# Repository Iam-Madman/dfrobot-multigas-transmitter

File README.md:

# DFRobot Multi-Gas Transmitter

An industrial-grade, multi-phase gas monitoring system implementing the Modbus RTU protocol over RS-485. This repository serves as a monorepo containing everything from the initial rapid hardware prototypes to production-ready firmware and hardware fabrication files.

---

## Repository Structure

The project separates hardware development from firmware development ecosystems across distinct execution phases:

```text
.
├── fabrication/                 
└── firmware/
    ├── arduino_nano_firmware/   
    └── bluepill_firmware/

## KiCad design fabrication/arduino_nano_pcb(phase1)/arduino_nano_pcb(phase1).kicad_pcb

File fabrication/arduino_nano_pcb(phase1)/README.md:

## Phase 1 Hardware Prototyping

The Phase 1 board utilizes an Arduino Nano baseboard designed for rapid validation of the TM1637 display interface and the DFRobot gas sensor lines. The traces have been widened to optimized thresholds (0.8mm–1.0mm) to allow for reliable manual mechanical isolation milling.

### Board Previews

| |
|---|
|  |
|  |

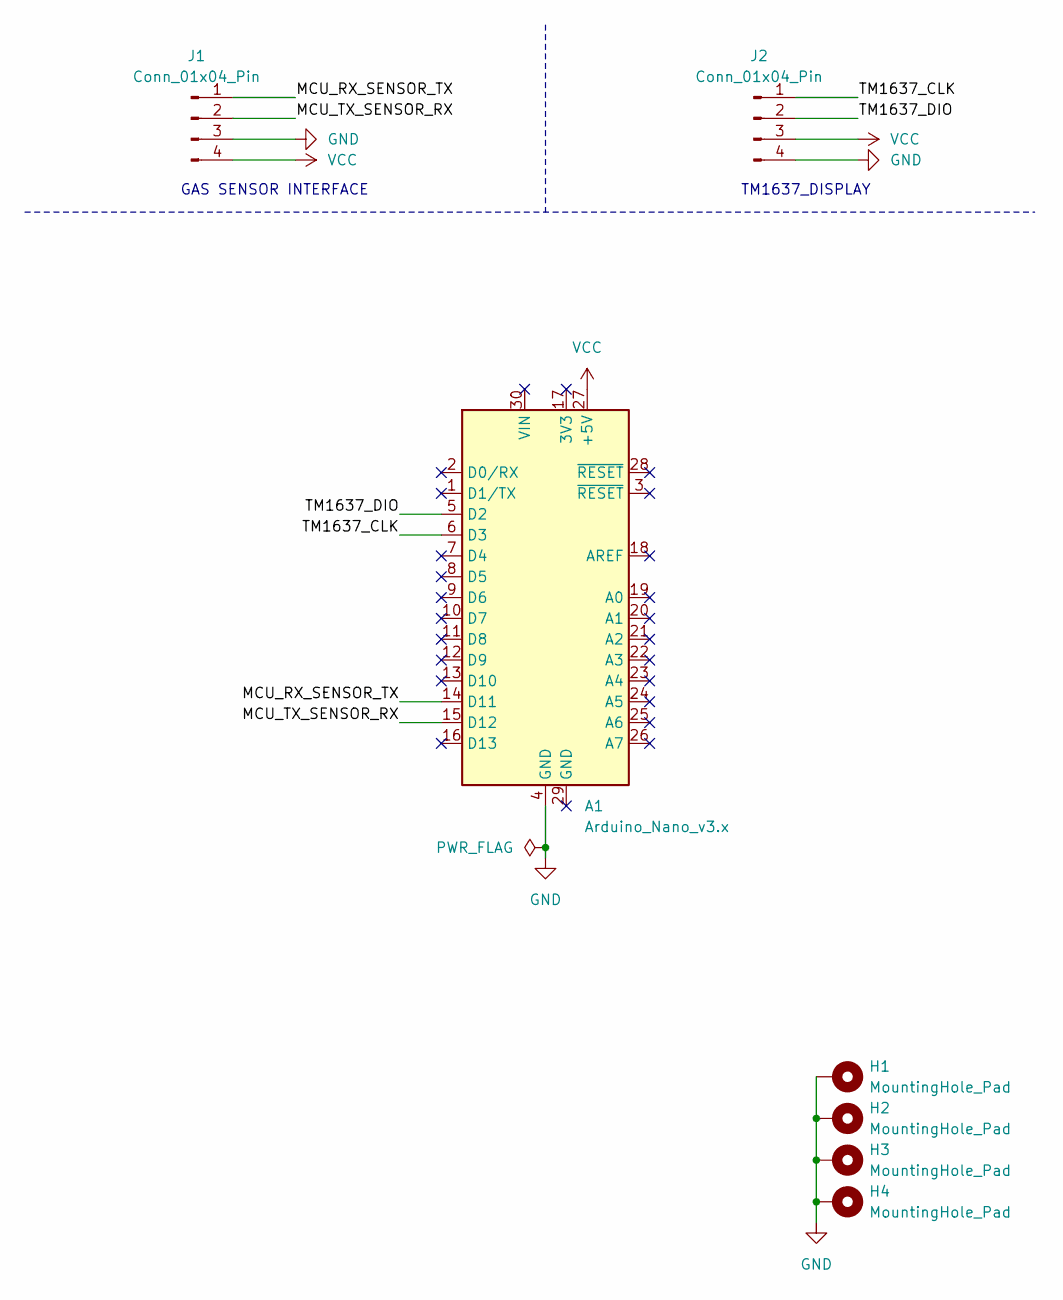
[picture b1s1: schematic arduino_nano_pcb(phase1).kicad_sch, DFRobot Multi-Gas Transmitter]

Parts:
A1: Arduino_Nano_v3.x; Arduino_Nano
H1, H2, H3, H4: MountingHole_Pad; MountingHole_5mm_Pad_TopBottom
J1: Conn_01x04_Pin; PinHeader_1x04_P2.54mm_Horizontal
J2: Conn_01x04_Pin; TM1637

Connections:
/MCU_RX_SENSOR_TX: A1.14 (D11), J1.1
/MCU_TX_SENSOR_RX: A1.15 (D12), J1.2
/TM1637_CLK: A1.6 (D3), J2.1
/TM1637_DIO: A1.5 (D2), J2.2
GND: A1.4 (GND), H1.1 (1_1), H2.1 (1_1), H3.1 (1_1), H4.1 (1_1), J1.3, J2.4
VCC: A1.27 (+5V), J1.4, J2.3

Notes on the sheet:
TM1637_DISPLAY
GAS SENSOR INTERFACE

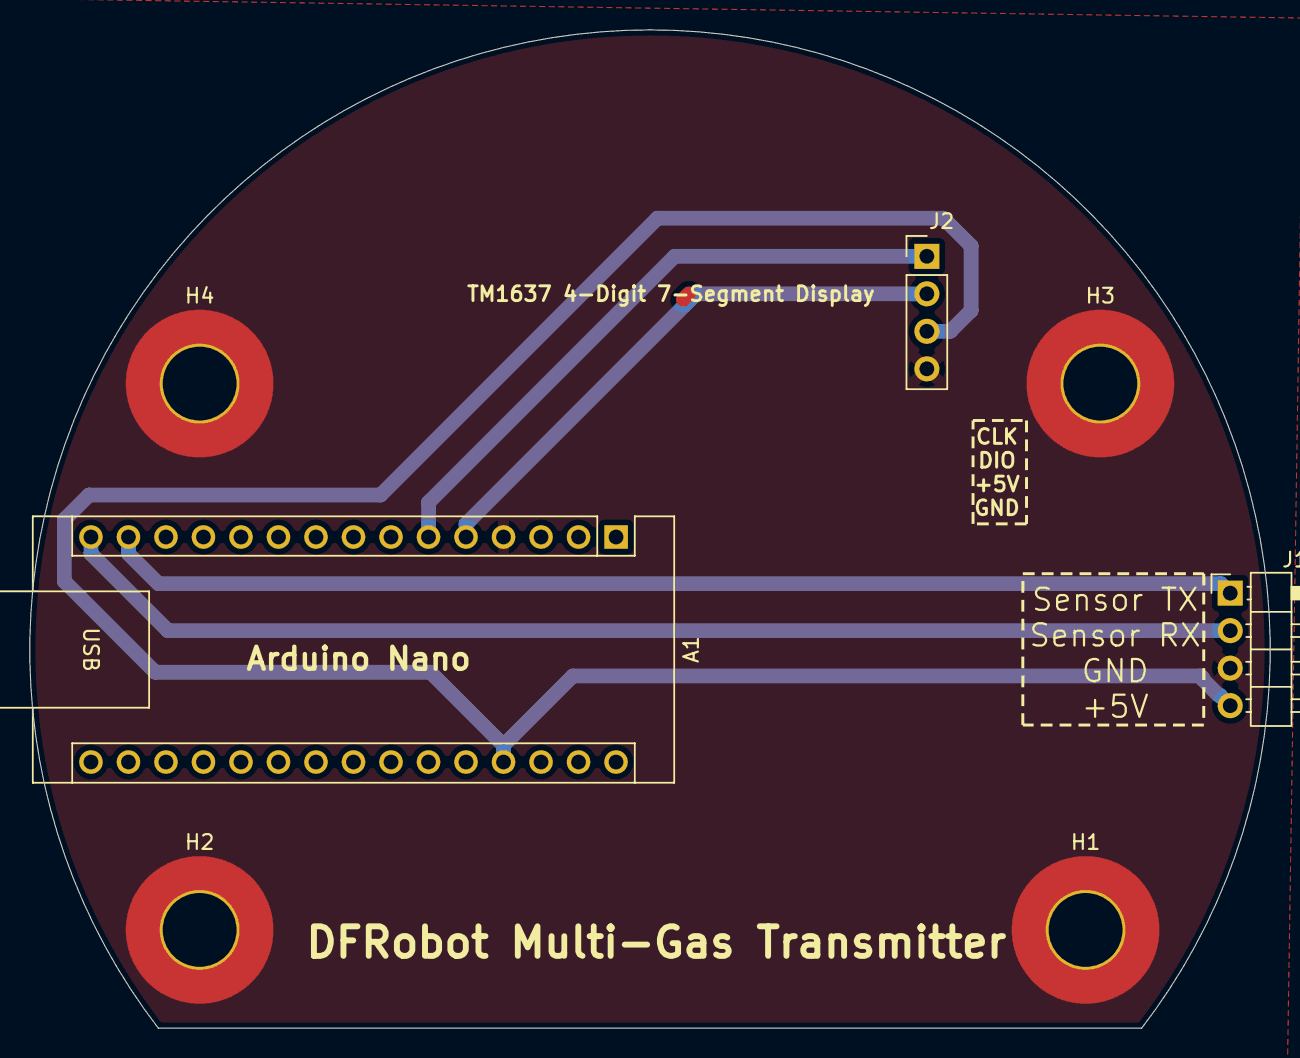
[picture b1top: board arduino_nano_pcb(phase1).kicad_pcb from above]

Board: 2 copper layers, 84.0 x 67.6 mm, 7 parts (0 on the bottom side), 6 nets.

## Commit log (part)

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2026-06-18 fixed .gitignore
2026-06-18 Force remove .vscode from tracking
2026-06-18 Remove firmware .vscode from tracking and update gitignore
2026-06-18 feat(fixed_adc_dma): adc dma has been fixed to include a double buffer
